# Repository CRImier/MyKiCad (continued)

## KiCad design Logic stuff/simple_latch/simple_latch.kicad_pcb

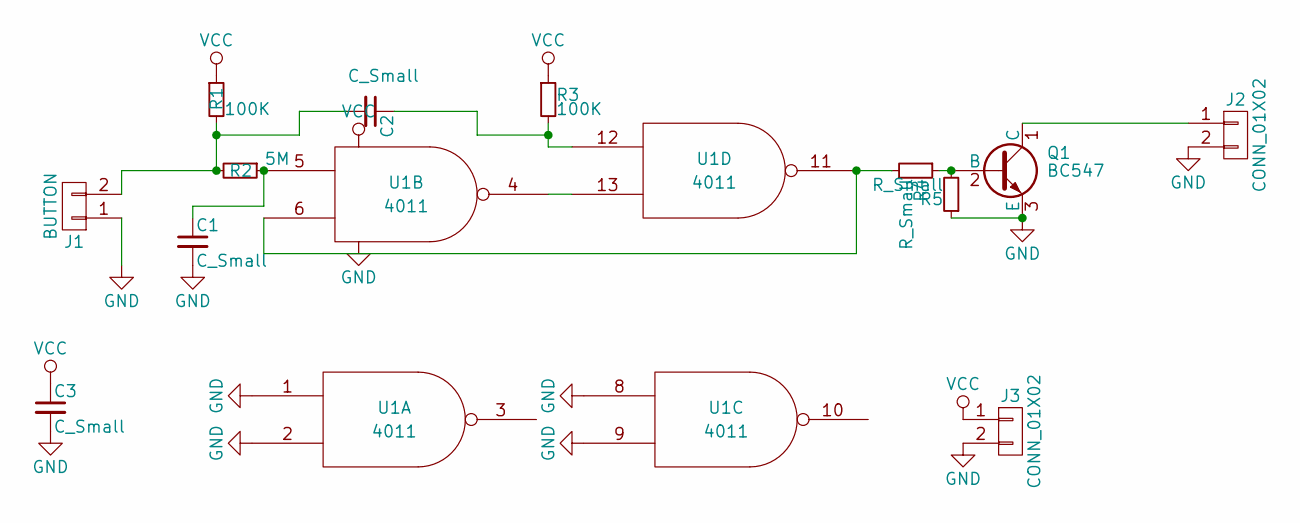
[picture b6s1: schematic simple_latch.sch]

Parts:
C1, C2, C3: C_Small; C_0603_HandSoldering
J1: BUTTON; Pin_Header_Straight_1x02_Pitch2.54mm
J2, J3: CONN_01X02; Pin_Header_Straight_1x02_Pitch2.54mm
Q1: BC547; SOT-23_BC847B_Handsoldering
R1, R3: 100K; R_0603_HandSoldering
R2: 5M; R_0603_HandSoldering
R4, R5: R_Small; R_0603_HandSoldering
U1: 4011; SOIC-14_3.9x8.7mm_Pitch1.27mm

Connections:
GND: C1.2, C3.2, J1.1, J2.2, J3.2, Q1.3 (E), R5.1, U1.1, U1.2, U1.7 (VSS), U1.8, U1.9
unnamed: C1.1, R2.1, U1.5
unnamed: C2.1, R3.2, U1.12
unnamed: C2.2, J1.2, R1.2, R2.2
unnamed: J2.1, Q1.1 (C)
unnamed: Q1.2 (B), R4.1, R5.2
unnamed: R4.2, U1.6, U1.11
unnamed: U1.4, U1.13
VCC: C3.1, J3.1, R1.1, R3.1, U1.14 (VDD)

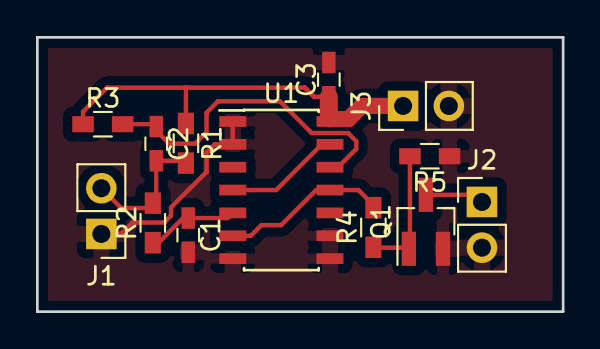
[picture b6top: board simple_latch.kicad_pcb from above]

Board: 2 copper layers, 29.2 x 15.2 mm, 13 parts (0 on the bottom side), 9 nets.

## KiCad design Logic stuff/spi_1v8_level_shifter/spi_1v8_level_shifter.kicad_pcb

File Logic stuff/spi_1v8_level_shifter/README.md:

# SPI 1.8V level shifter

A small board that level shifts a single SPI channel from 5V/3.3V to 1.8V and provides 1.8 power to the target.
Useful for, say, flashing SPI memory chips in-circuit. Uses two GTL2002 ICs in TSSOP.

- PCB size: 27.85mm*16mm
- Layer count: 2

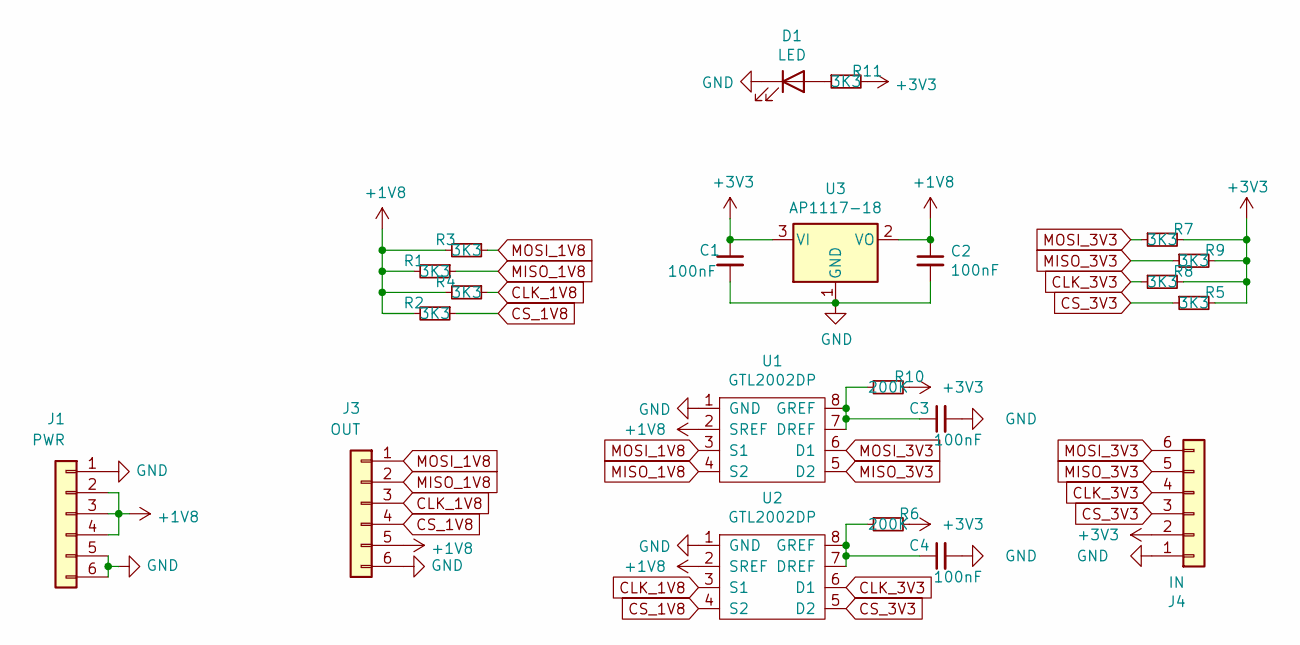
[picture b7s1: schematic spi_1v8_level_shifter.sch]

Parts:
C1, C2, C3, C4: 100nF; C_0603_1608Metric
D1: LED; LED_0805_2012Metric
J1: PWR; PinHeader_1x06_P2.54mm_Vertical
J3: OUT; PinHeader_1x06_P2.54mm_Vertical
J4: IN; PinHeader_1x06_P2.54mm_Vertical
R1, R2, R3, R4, R5, R7, R8, R9, R11: 3K3; R_0402_1005Metric
R6, R10: 200K; R_0402_1005Metric
U1, U2: GTL2002DP; TSSOP-8_3x3mm_P0.65mm
U3: AP1117-18; SOT-223-3_TabPin2

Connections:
+1V8: C2.1, J1.2, J1.3, J1.4, J3.5, R1.2, R2.2, R3.2, R4.2, U1.2 (SREF), U2.2 (SREF), U3.2 (VO)
+3V3: C1.1, J4.2, R5.2, R6.2, R7.2, R8.2, R9.2, R10.2, R11.2, U3.3 (VI)
CLK_1V8: J3.3, R4.1, U2.3 (S1)
CLK_3V3: J4.4, R8.1, U2.6 (D1)
CS_1V8: J3.4, R2.1, U2.4 (S2)
CS_3V3: J4.3, R5.1, U2.5 (D2)
GND: C1.2, C2.2, C3.2, C4.2, D1.1 (K), J1.1, J1.5, J1.6, J3.6, J4.1, U1.1 (GND), U2.1 (GND), U3.1 (GND)
MISO_1V8: J3.2, R1.1, U1.4 (S2)
MISO_3V3: J4.5, R9.1, U1.5 (D2)
MOSI_1V8: J3.1, R3.1, U1.3 (S1)
MOSI_3V3: J4.6, R7.1, U1.6 (D1)
unnamed: C3.1, R10.1, U1.7 (DREF), U1.8 (GREF)
unnamed: C4.1, R6.1, U2.7 (DREF), U2.8 (GREF)
unnamed: D1.2 (A), R11.1

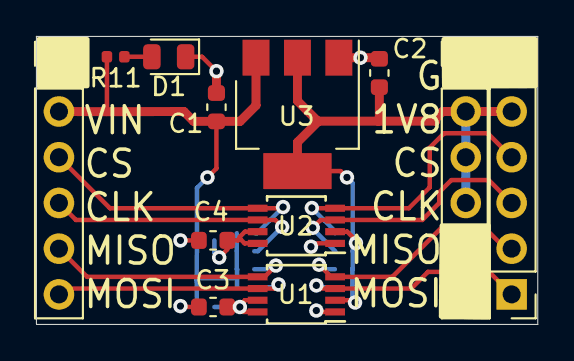
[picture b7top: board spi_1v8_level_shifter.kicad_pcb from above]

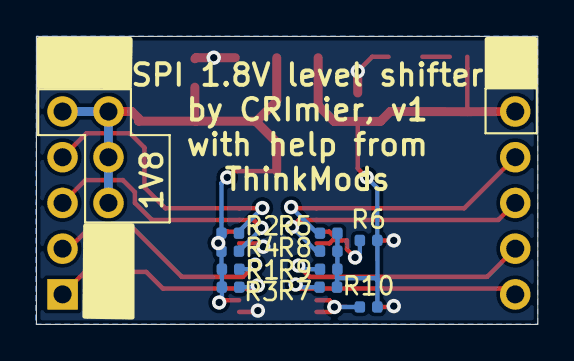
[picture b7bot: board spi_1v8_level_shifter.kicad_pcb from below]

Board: 2 copper layers, 27.8 x 16.0 mm, 22 parts (10 on the bottom side), 14 nets.
